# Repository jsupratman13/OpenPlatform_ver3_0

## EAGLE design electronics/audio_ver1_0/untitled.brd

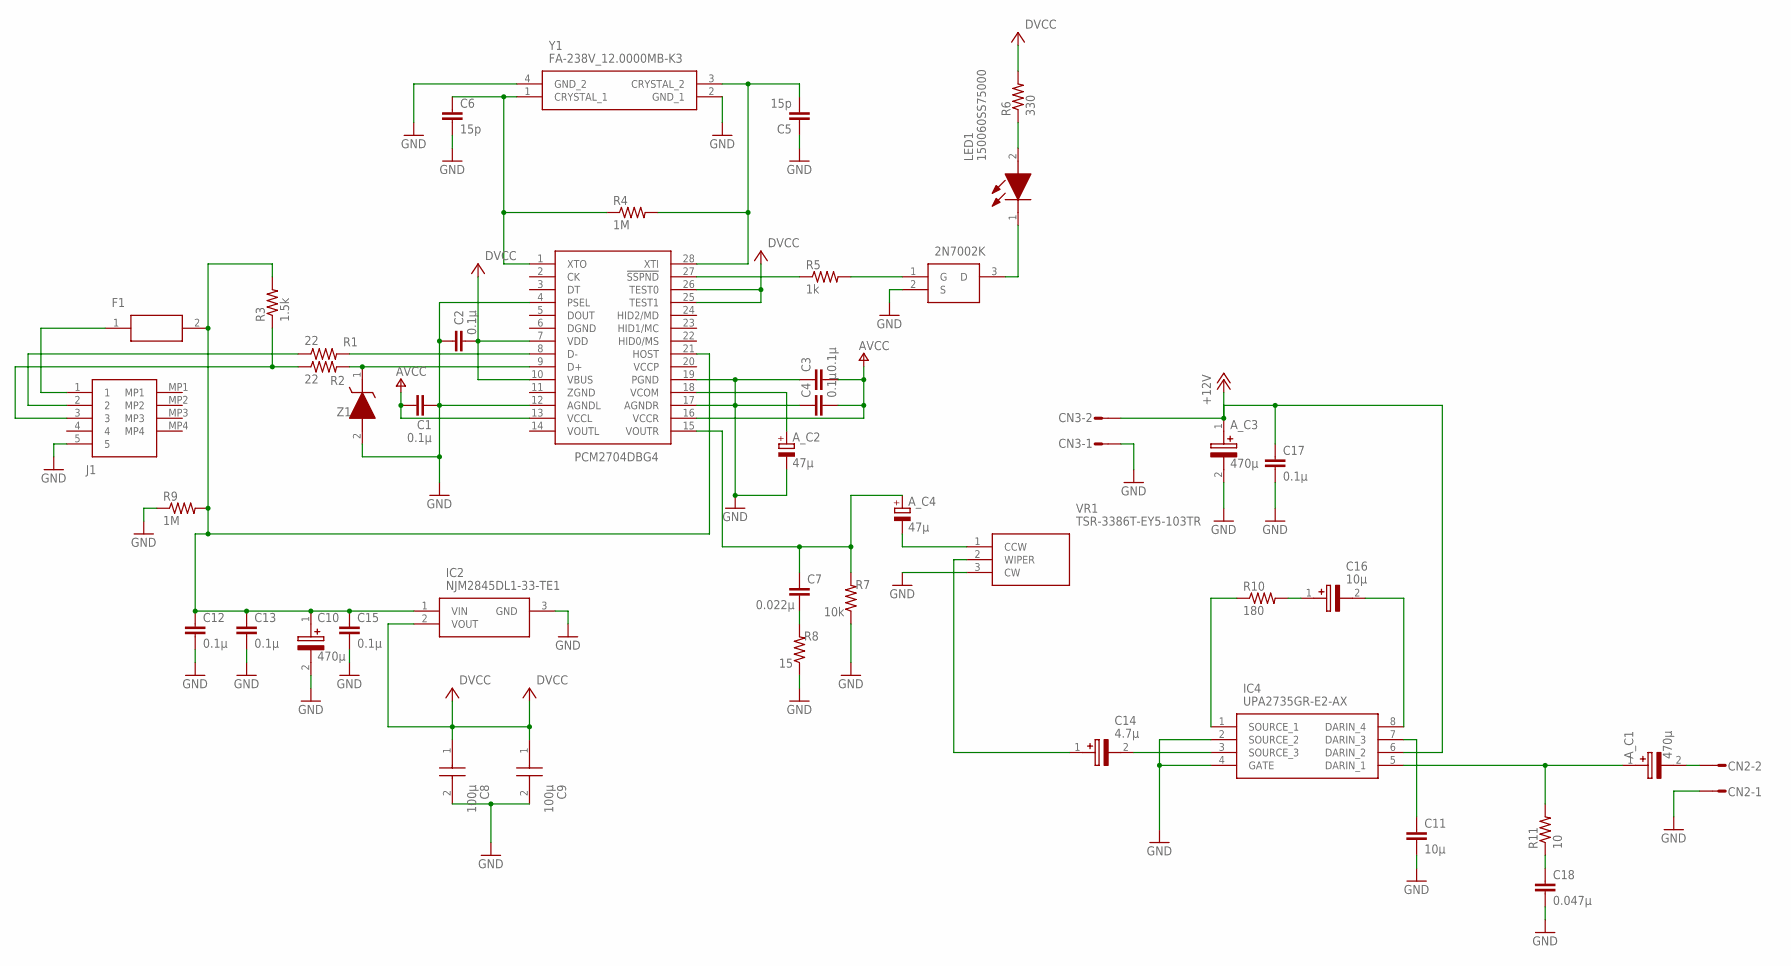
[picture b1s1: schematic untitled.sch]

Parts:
A_C1, A_C3: 470μ; CAPPRD350W60D825H1150
A_C2, A_C4: 47μ; UFG1E470MEM
C1, C2, C3, C4, C12, C13, C15, C17: 0.1μ; C0603
C5, C6: 15p; C0603
C7: 0.022μ; C0603
C8, C9: 100μ; PK(5X11)
C10: 470μ; CAPPRD350W60D825H1150
C11: 10μ; 50F2D473J
C14: 4.7μ; CAPPRD200W50D525H1100
C16: 10μ; CAPPRD200W50D550H1250
C18: 0.047μ; 50F2D473J
CN2, CN3: S02P
F1: MICROSMD010-2; MICROSMD175F2
IC1: PCM2704DBG4; SOP65P780X200-28N
IC2: NJM2845DL1-33-TE1; TO-252-3-L1
IC3: 2N7002K; SOT65P210X110-3N
IC4: UPA2735GR-E2-AX; SOIC127P600X175-8N
J1: USB2066-05-RBHM-15-STB-00-00-A; USB206605RBHM15STB0000A
LED1: 150060SS75000; LEDC1608X80N
R1, R2: 22; R0603
R3: 1.5k; R0603
R4, R9: 1M; R0603
R5: 1k; R0603
R6: 330; R0603
R7: 10k; R0603
R8: 15; R0603
R10: 180; R0603
R11: 10; R0603
VR1: TSR-3386T-EY5-103TR; TSR3386TEY5103TR
Y1: FA-238V_12.0000MB-K3; FA238V120000MBK3
Z1: UDZVTE-175.1B; UDZVTE1751B

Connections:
+5V: C2.2, C8.1 (-), C9.1 (-), IC1.7 (VDD), IC1.10 (VBUS), IC1.25 (TEST1), IC1.26 (TEST0), IC2.2 (VOUT), R6.2
+12V: A_C3.1 (+), C17.1, CN3.2, IC4.6 (DARIN_2)
GND: A_C2.P$2 (-), A_C3.2 (-), C1.2, C2.1, C3.1, C4.1, C5.1, C6.2, C8.2 (+), C9.2 (+), C10.2 (-), C11.P$2 (2), C12.2, C13.2, C15.2, C17.2, C18.P$2 (2), CN2.1, CN3.1, IC1.4 (PSEL), IC1.12 (AGNDL), IC1.17 (AGNDR), IC1.19 (PGND), IC2.3 (GND), IC3.2 (S), IC4.2 (SOURCE_2), IC4.4 (GATE), J1.5, R7.1, R8.1, R9.1, VR1.3 (CW), Y1.2 (GND_1), Y1.4 (GND_2), Z1.2 (A)
unnamed: J1.3, R2.1, R3.1
unnamed: IC1.8 (D-), R1.2
unnamed: IC1.9 (D+), R2.2, Z1.1 (K)
unnamed: J1.2, R1.1
unnamed: A_C1.2 (-), CN2.2
unnamed: C14.1 (+), VR1.2 (WIPER)
unnamed: C16.1 (+), R10.2
unnamed: C5.2, IC1.28 (XTI), R4.2, Y1.3 (CRYSTAL_2)
unnamed: A_C4.P$2 (-), VR1.1 (CCW)
unnamed: A_C1.1 (+), IC4.5 (DARIN_1), R11.2
unnamed: IC1.27 (!SSPND), R5.1
unnamed: IC3.1 (G), R5.2
unnamed: LED1.2 (A), R6.1
unnamed: IC3.3 (D), LED1.1 (K)
unnamed: C14.2 (-), IC4.3 (SOURCE_3)
unnamed: A_C4.P$1 (+), C7.1, IC1.15 (VOUTR), R7.2
unnamed: C7.2, R8.2
unnamed: F1.1, J1.1
unnamed: C11.P$1 (1), IC4.7 (DARIN_3)
unnamed: C10.1 (+), C12.1, C13.1, C15.1, F1.2, IC1.21 (HOST), IC2.1 (VIN), R3.2, R9.2
unnamed: C18.P$1 (1), R11.1
unnamed: IC4.1 (SOURCE_1), R10.1
unnamed: C6.1, IC1.1 (XTO), R4.1, Y1.1 (CRYSTAL_1)
unnamed: C16.2 (-), IC4.8 (DARIN_4)
unnamed: A_C2.P$1 (+), IC1.18 (VCOM)
V+: C1.1, C3.2, C4.2, IC1.13 (VCCL), IC1.16 (VCCR)

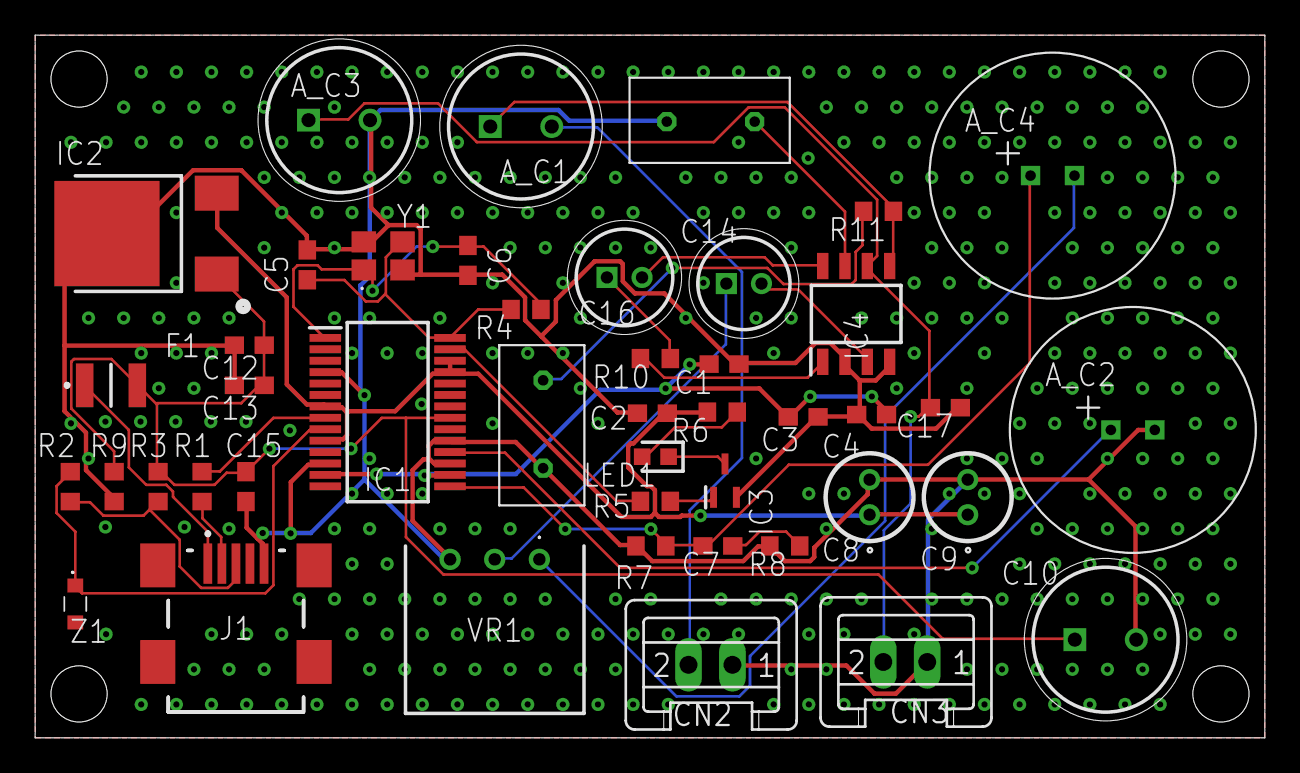
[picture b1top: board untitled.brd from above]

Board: 2 copper layers, 70.0 x 40.0 mm, 45 parts (0 on the bottom side), 29 nets.

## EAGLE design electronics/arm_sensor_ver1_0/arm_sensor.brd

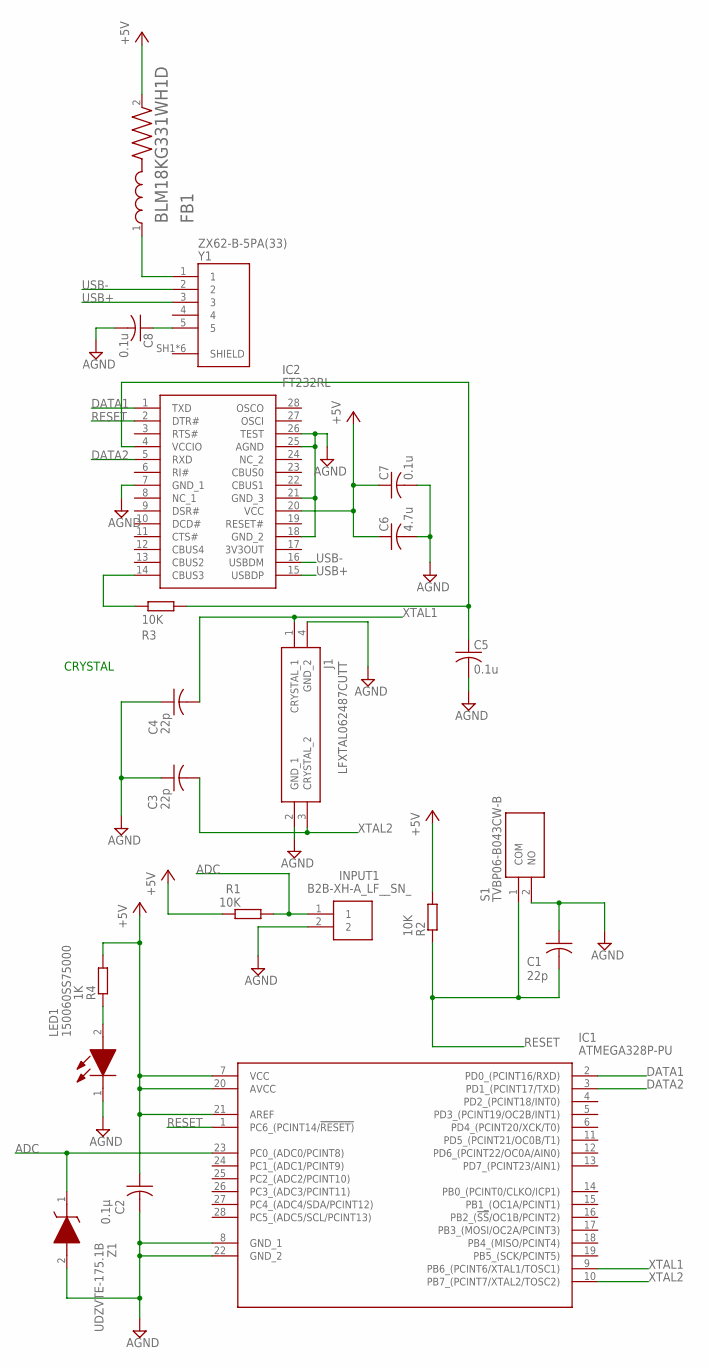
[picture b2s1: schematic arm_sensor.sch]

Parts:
C1, C3, C4: 22p; C1608
C2: 0.1μ; C1608
C5, C7, C8: 0.1u; C1608
C6: 4.7u; C1608
FB1: BLM18KG331WH1D; BEADC1608X75N
IC1: ATMEGA328P-PU; DIP794W53P254L3467H457Q28N
IC2: FT232RL; SOP65P778X200-28N@1
INPUT1: B2B-XH-A_LF__SN_; SHDR2W64P0X250_1X2_740X575X700
J1: LFXTAL062487CUTT
LED1: 150060SS75000; LEDC1608X80N
R1, R2, R3: 10K; R0603
R4: 1K; R0603
S1: TVBP06-B043CW-B; TVBP06B043CWB
Y1: ZX62-B-5PA(33); HRS_ZX62-B-5PA(33)
Z1: UDZVTE-175.1B; UDZVTE1751B

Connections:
+5V: C2.1, C6.1, C7.1, FB1.2, IC1.7 (VCC), IC1.20 (AVCC), IC1.21 (AREF), IC2.20 (VCC), R1.2, R2.2, R4.2
ADC: IC1.23 (PC0_(ADC0/PCINT8)), INPUT1.1, R1.1, Z1.1 (K)
AGND: C1.1, C2.2, C3.1, C4.1, C5.2, C6.2, C7.2, C8.2, IC1.8 (GND_1), IC1.22 (GND_2), IC2.18 (GND_2), IC2.21 (GND_3), IC2.25 (AGND), IC2.26 (TEST), INPUT1.2, J1.2 (GND_1), J1.4 (GND_2), LED1.1 (K), S1.2 (NO), Z1.2 (A)
DATA1: IC1.2 (PD0_(PCINT16/RXD)), IC2.1 (TXD)
DATA2: IC1.3 (PD1_(PCINT17/TXD)), IC2.5 (RXD)
unnamed: LED1.2 (A), R4.1
unnamed: FB1.1, Y1.1
unnamed: C8.1, Y1.5
unnamed: IC2.14 (CBUS3), R3.1
RESET: C1.2, IC1.1 (PC6_(PCINT14/!RESET)), IC2.2 (DTR#), R2.1, S1.1 (COM)
RS485_3V3: C5.1, R3.2
USB+: IC2.15 (USBDP), Y1.3
USB-: IC2.16 (USBDM), Y1.2
XTAL1: C4.2, IC1.9 (PB6_(PCINT6/XTAL1/TOSC1)), J1.1 (CRYSTAL_1)
XTAL2: C3.2, IC1.10 (PB7_(PCINT7/XTAL2/TOSC2)), J1.3 (CRYSTAL_2)

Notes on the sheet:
CRYSTAL

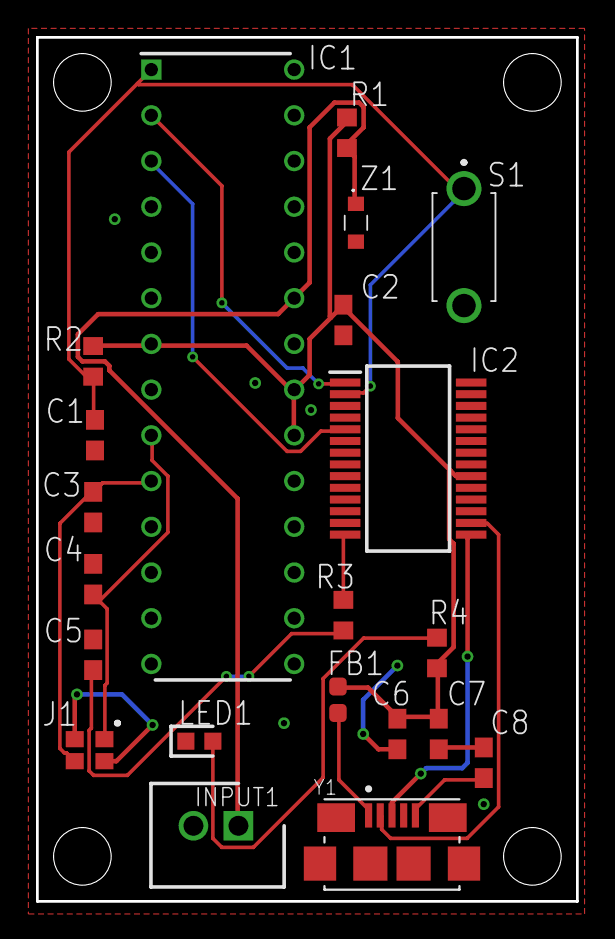
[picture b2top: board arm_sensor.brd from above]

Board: 2 copper layers, 30.0 x 48.0 mm, 21 parts (0 on the bottom side), 15 nets.

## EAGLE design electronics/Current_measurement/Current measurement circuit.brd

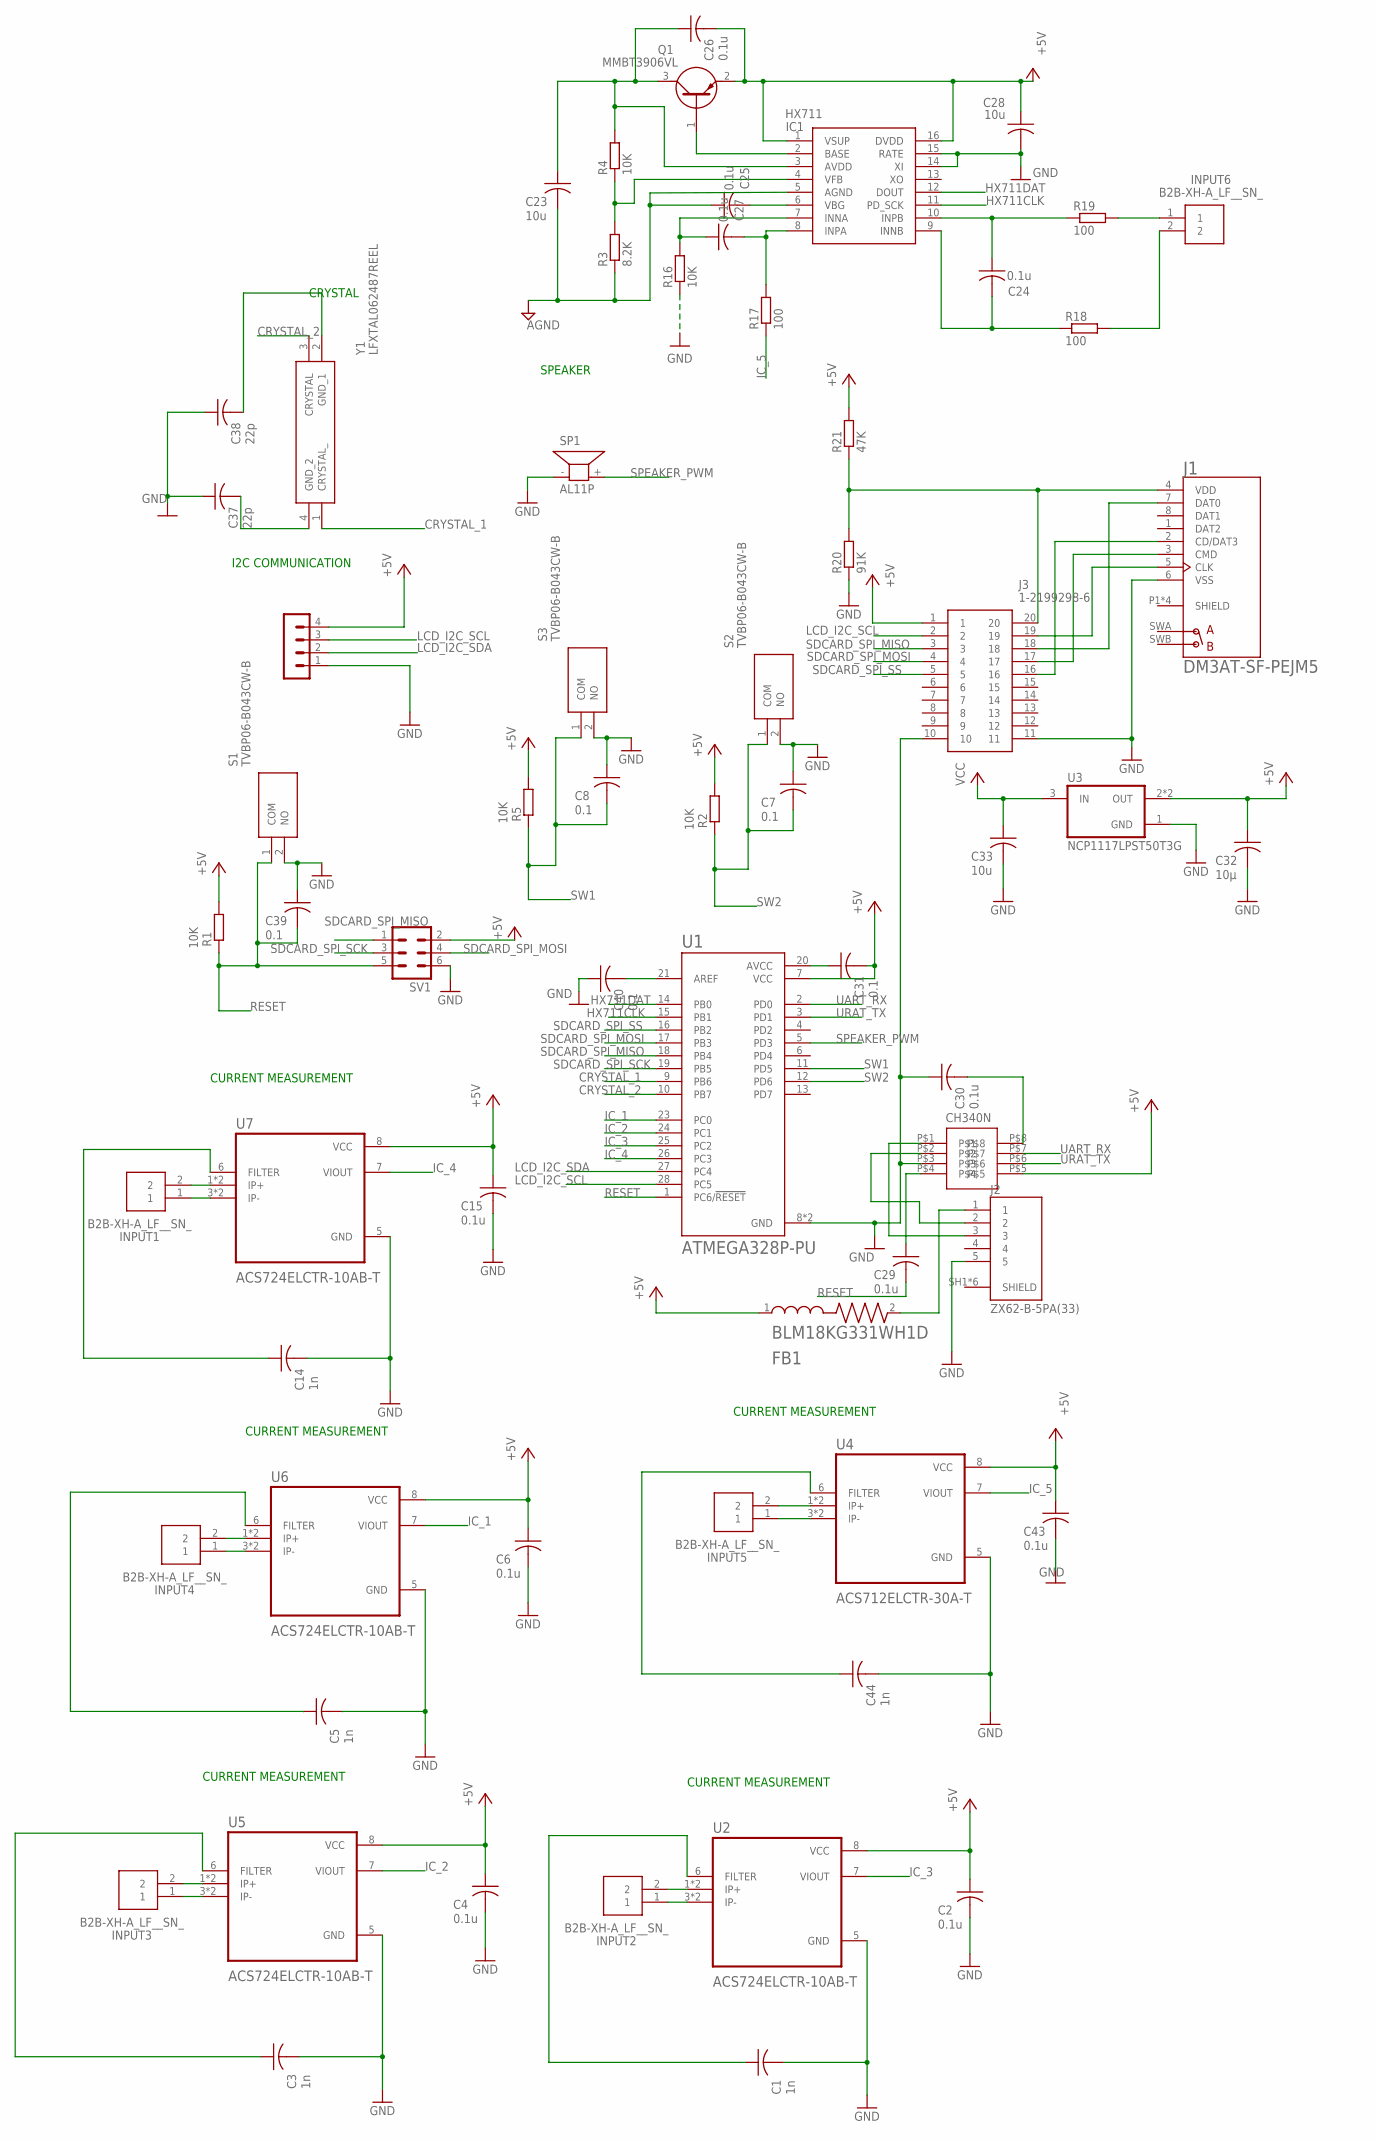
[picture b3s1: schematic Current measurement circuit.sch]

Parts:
C1, C3, C5, C14, C44: 1n; C1608
C2, C4, C6, C15, C24, C25, C26, C27, C29, C30, C43: 0.1u; C1608
C7, C8, C31, C39, C40: 0.1; C1608
C23, C28, C33: 10u; C1608
C32: 10μ; C1608
C37, C38: 22p; C1608
FB1: BLM18KG331WH1D; BEADC1608X75N
IC1: HX711; SOIC127P600X160-16N
INPUT1, INPUT2, INPUT3, INPUT4, INPUT5, INPUT6: B2B-XH-A_LF__SN_; SHDR2W64P0X250_1X2_740X575X700
J1: DM3AT-SF-PEJM5; HRS_DM3AT-SF-PEJM5
J2: ZX62-B-5PA(33); HRS_ZX62-B-5PA(33)
J3: 1-2199298-6; DIPS762W70P254L2540H510Q20N
Q1: MMBT3906VL; SOT95P230X110-3N
R1, R2, R4, R5, R16: 10K; R0603
R3: 8.2K; R0603
R17, R18, R19: 100; R0603
R20: 91K; R0603
R21: 47K; R0603
S1, S2, S3: TVBP06-B043CW-B; TVBP06B043CWB
SP1: AL11P
SV1: MA03-2
SV4: MA04-1
U1: ATMEGA328P-PU; DIP794W46P254L2967H457Q28B
U2, U5, U6, U7: ACS724ELCTR-10AB-T; SOIC127P600X175-8N
U3: NCP1117LPST50T3G; SOT230P700X180-4N
U4: ACS712ELCTR-30A-T; SOIC127P600X175-8N
U$1: CH340N
Y1: LFXTAL062487REEL

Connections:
+5V: C2.1, C4.1, C6.1, C15.1, C26.2, C28.1, C31.2, C32.1, C43.1, FB1.1, IC1.1 (VSUP), IC1.16 (DVDD), J3.1, Q1.2 (E), R1.2, R2.2, R5.2, R21.2, SV1.2, SV4.4, U1.7 (VCC), U2.8 (VCC), U3.2 (OUT), U3.4 (OUT), U4.8 (VCC), U5.8 (VCC), U6.8 (VCC), U7.8 (VCC), U$1.P$5
AGND: C23.2, C25.1, IC1.5 (AGND), R3.1
CRYSTAL_1: U1.9 (PB6), Y1.1 (CRYSTAL_)
CRYSTAL_2: U1.10 (PB7), Y1.3 (CRYSTAL)
GND: C1.2, C2.2, C3.2, C4.2, C5.2, C6.2, C7.1, C8.1, C14.2, C15.2, C28.2, C30.1, C32.2, C33.2, C37.1, C38.1, C39.1, C40.1, C43.2, C44.2, IC1.14 (XI), IC1.15 (RATE), J1.6 (VSS), J2.5, J3.10, J3.11, R16.1, R20.1, S1.2 (NO), S2.2 (NO), S3.2 (NO), SP1.- (1), SV1.6, SV4.1, U1.8 (GND), U1.22 (GND), U2.5 (GND), U3.1 (GND), U4.5 (GND), U5.5 (GND), U6.5 (GND), U7.5 (GND), U$1.P$3
HX711CLK: IC1.11 (PD_SCK), U1.15 (PB1)
HX711DAT: IC1.12 (DOUT), U1.14 (PB0)
IC_1: U1.23 (PC0), U6.7 (VIOUT)
IC_2: U1.24 (PC1), U5.7 (VIOUT)
IC_3: U1.25 (PC2), U2.7 (VIOUT)
IC_4: U1.26 (PC3), U7.7 (VIOUT)
IC_5: R17.1, U4.7 (VIOUT)
LCD_I2C_SCL: J3.2, SV4.3, U1.28 (PC5)
LCD_I2C_SDA: SV4.2, U1.27 (PC4)
unnamed: C29.1, U$1.P$4
unnamed: C37.2, Y1.4 (GND_2)
unnamed: C38.2, Y1.2 (GND_1)
unnamed: C1.1, U2.6 (FILTER)
unnamed: C3.1, U5.6 (FILTER)
unnamed: C40.2, U1.21 (AREF)
unnamed: C31.1, U1.20 (AVCC)
unnamed: INPUT5.2, U4.1 (IP+), U4.2 (IP+)
unnamed: INPUT5.1, U4.3 (IP-), U4.4 (IP-)
unnamed: C44.1, U4.6 (FILTER)
unnamed: INPUT2.2, U2.1 (IP+), U2.2 (IP+)
unnamed: INPUT2.1, U2.3 (IP-), U2.4 (IP-)
unnamed: C5.1, U6.6 (FILTER)
unnamed: INPUT3.2, U5.1 (IP+), U5.2 (IP+)
unnamed: INPUT3.1, U5.3 (IP-), U5.4 (IP-)
unnamed: INPUT1.2, U7.1 (IP+), U7.2 (IP+)
unnamed: INPUT1.1, U7.3 (IP-), U7.4 (IP-)
unnamed: C14.1, U7.6 (FILTER)
unnamed: C27.1, IC1.7 (INNA), R16.2
unnamed: C27.2, IC1.8 (INPA), R17.2
unnamed: IC1.2 (BASE), Q1.1 (B)
unnamed: C25.2, IC1.6 (VBG)
unnamed: C23.1, C26.1, IC1.3 (AVDD), Q1.3 (C), R4.2
unnamed: INPUT6.1, R19.2
unnamed: J1.2 (CD/DAT3), J3.16
unnamed: J1.3 (CMD), J3.17
unnamed: J1.5 (CLK), J3.19
unnamed: IC1.4 (VFB), R3.2, R4.1
unnamed: J1.7 (DAT0), J3.18
unnamed: J2.3, U$1.P$1
unnamed: C24.1, IC1.10 (INPB), R19.1
unnamed: C30.2, U$1.P$8
unnamed: INPUT6.2, R18.2
unnamed: C24.2, IC1.9 (INNB), R18.1
unnamed: J2.2, U$1.P$2
unnamed: FB1.2, J2.1
unnamed: J1.4 (VDD), J3.20, R20.2, R21.1
unnamed: INPUT4.2, U6.1 (IP+), U6.2 (IP+)
unnamed: INPUT4.1, U6.3 (IP-), U6.4 (IP-)
RESET: C29.2, C39.2, R1.1, S1.1 (COM), SV1.5, U1.1 (PC6/!RESET)
SDCARD_SPI_MISO: J3.3, SV1.1, U1.18 (PB4)
SDCARD_SPI_MOSI: J3.4, SV1.4, U1.17 (PB3)
SDCARD_SPI_SCK: SV1.3, U1.19 (PB5)
SDCARD_SPI_SS: J3.5, U1.16 (PB2)
SPEAKER_PWM: SP1.+ (2), U1.5 (PD3)
SW1: C8.2, R5.1, S3.1 (COM), U1.11 (PD5)
SW2: C7.2, R2.1, S2.1 (COM), U1.12 (PD6)
UART_RX: U1.2 (PD0), U$1.P$7
URAT_TX: U1.3 (PD1), U$1.P$6
VCC: C33.1, U3.3 (IN)

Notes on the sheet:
CRYSTAL
SPEAKER
I2C COMMUNICATION
CURRENT MEASUREMENT

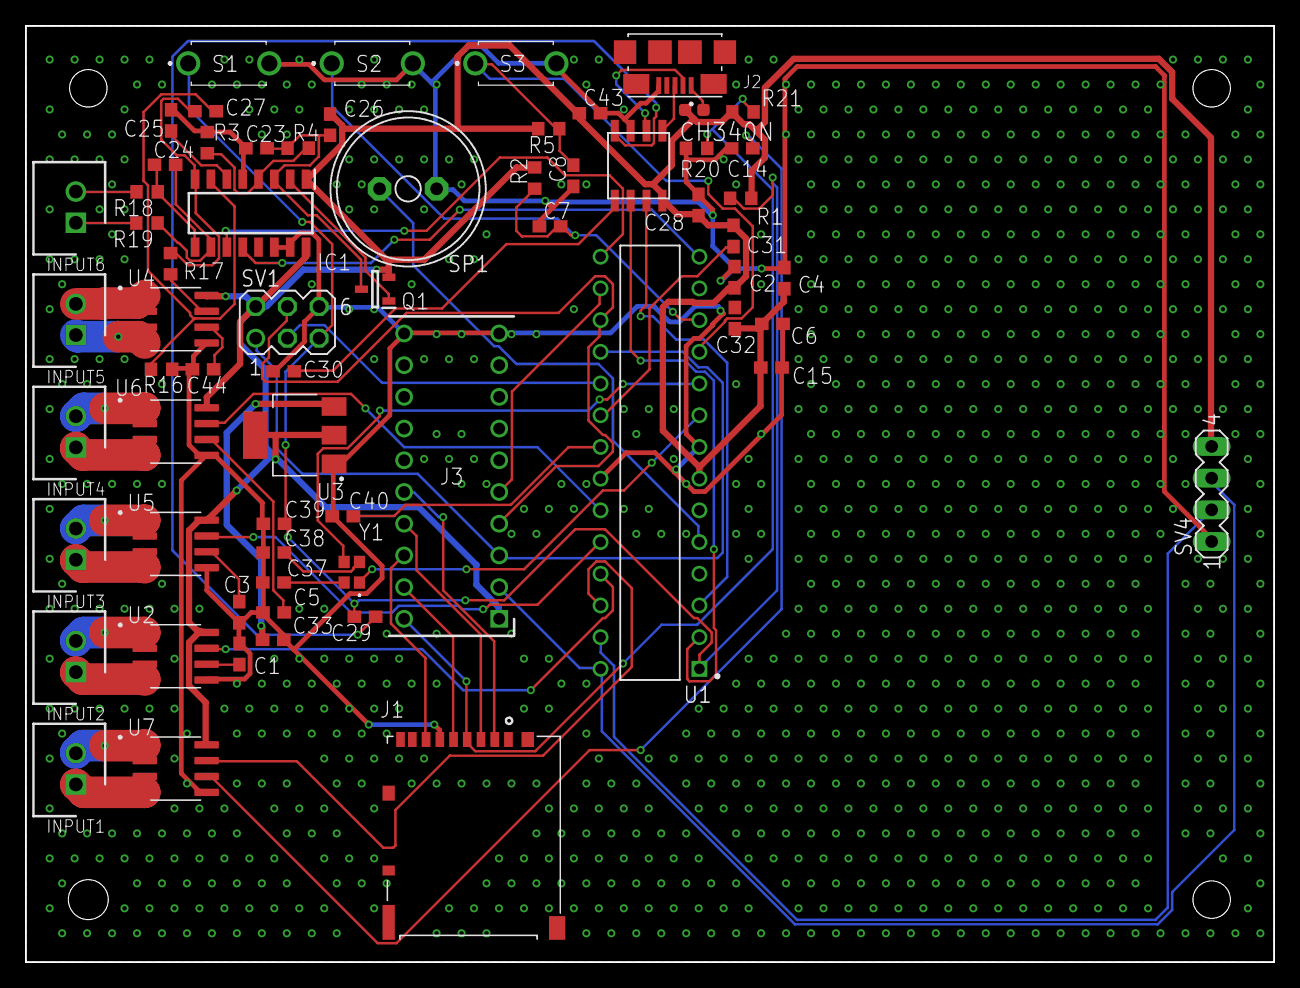
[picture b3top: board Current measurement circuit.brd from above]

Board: 2 copper layers, 100.0 x 75.0 mm, 65 parts (0 on the bottom side), 64 nets.

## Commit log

2021-12-29 Change ankle pitch screws
2021-12-29 Update HTML
2021-12-31 Add Fusion360 model
2022-04-14 push arm_sensor_ver1_0
2022-04-29 push audio
2022-04-30 push audio_ver1_0
2022-09-24 Moved the circuit data storage location
2023-06-06 draft
